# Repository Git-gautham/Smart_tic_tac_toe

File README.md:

# ESP8266 XOX Game (Tic-Tac-Toe)

A two-player Tic-Tac-Toe game built using an ESP8266 NodeMCU board, 5 physical push buttons, and a Wi-Fi-based web interface — no need for external hosting or filesystem upload!

## 🔧 Features

- 🕹️ **Real-time interaction** with physical buttons:
  - `UP`, `LEFT`, `RIGHT`, `SELECT`, and `DOWN` (optional)
- 🌐 **Access via browser** — ESP8266 runs in AP (Access Point) mode
- 🧠 Smart in-browser UI:
  - Grid highlighting with cursor
  - Tracks turns for `X` and `O`
  - Win/draw detection
  - Scoreboard
  - "Next Game" and "Reset Score" buttons
- 🪛 Simple, detachable hardware via header pins
- 🖥️ No LittleFS or SPIFFS required

---

## 📷 Screenshot

---

## 🖥️ Web Interface

Once powered on:
- Connect to Wi-Fi: `XOX_Game` (password: `12345678`)
- Open browser and go to: [http://192.168.4.1](http://192.168.4.1)

---

## 🔌 Hardware Setup

| Function | NodeMCU Pin | GPIO | Status |
|----------|-------------|------|--------|
| Up       | D1          | 5    | ✅ Connected |
| Left     | D2          | 4    | ✅ Connected |
| Right    | D5          | 14   | ✅ Connected |
| Select   | D6          | 12   | ✅ Connected |
| Down     | D7          | 13   | ✅ Connected |

**ESP8266 Dev Board:** NodeMCU v1.0 (ESP-12E module)  
**Buttons:** Tactile push buttons
**Hardware simulation :

!!Down button is not placed due to certain technical difficulties

---

## 🛠️ Schematic (KiCad)

The PCB includes:
- Female headers to plug/unplug NodeMCU
- 5 push buttons connected to GPIOs
- All traces on the bottom side

---

## 🚀 Getting Started

1. Open `src/xox_game.ino` in Arduino IDE
2. Select board: `NodeMCU 1.0 (ESP-12E Module)`
3. Upload the sketch
4. Connect power, join Wi-Fi, and play!

## 🧠 TODO / Improvements

- Add buzzer feedback or LED indicators
- Expand to multiplayer over web (ESP8266 WebSocket)
- Add OLED support

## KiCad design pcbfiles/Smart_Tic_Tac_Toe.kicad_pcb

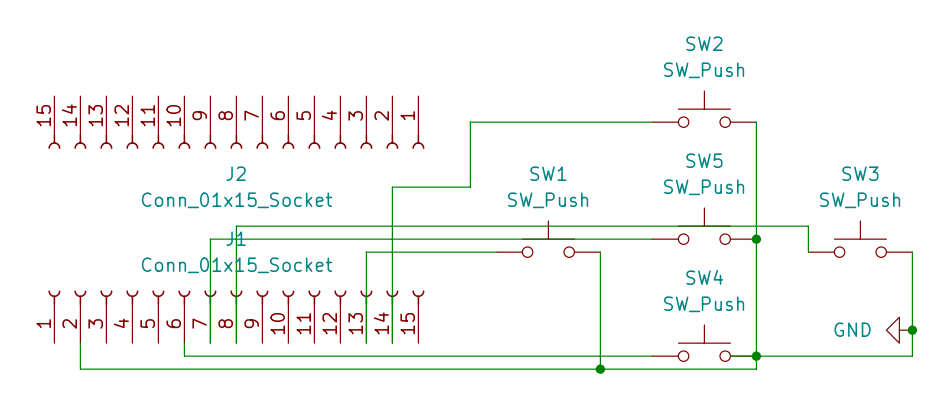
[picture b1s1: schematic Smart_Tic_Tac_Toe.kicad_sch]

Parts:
J1, J2: Conn_01x15_Socket; PinSocket_1x15_P2.54mm_Vertical
SW1, SW2, SW3, SW4, SW5: SW_Push; SW_PUSH_6mm

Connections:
GND: J1.2, SW1.2, SW2.2, SW3.2, SW4.2, SW5.2
unnamed: J1.6, SW4.1
unnamed: J1.7, SW5.1
unnamed: J1.8, SW3.1
unnamed: J1.13, SW1.1
unnamed: J1.14, SW2.1

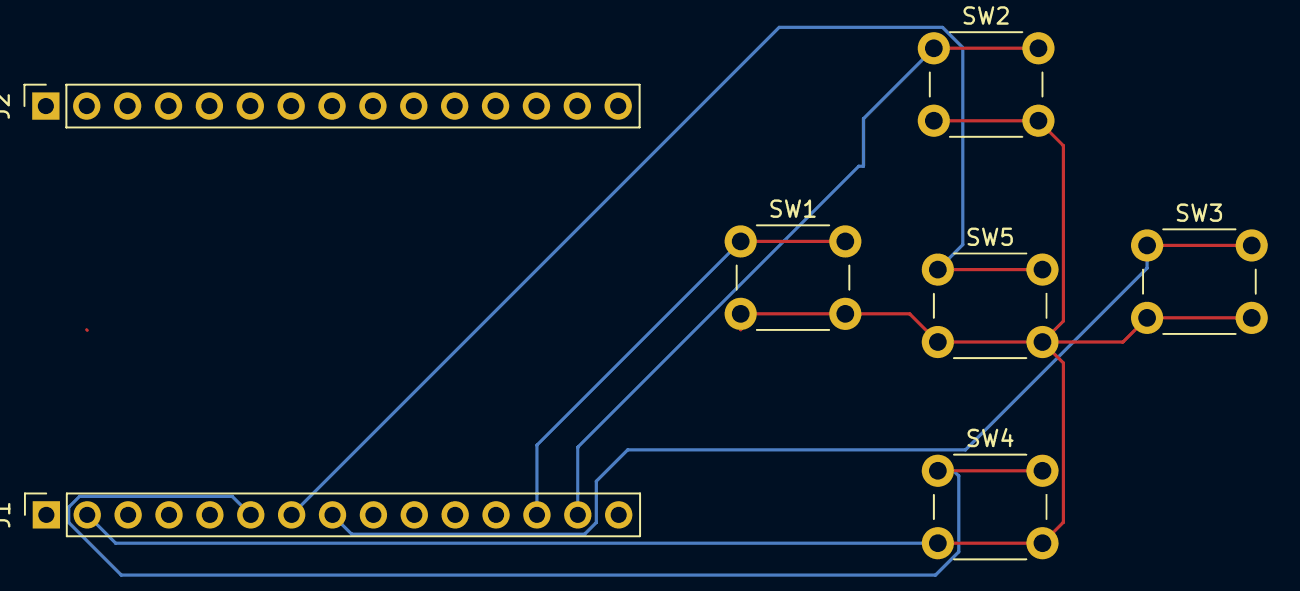
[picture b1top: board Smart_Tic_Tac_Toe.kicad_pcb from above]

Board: 2 copper layers, 7 parts (0 on the bottom side), 6 nets.

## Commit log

2025-06-12 Rename WhatsApp Image 2025-06-12 at 11.34.13_568ad91c.jpg to screenshot1
2025-06-12 Rename WhatsApp Image 2025-06-12 at 11.34.15_2e803093.jpg to circuitdemo
2025-06-12 Rename WhatsApp Image 2025-06-12 at 11.34.14_3d9d58dc.jpg to screenshot2
2025-06-12 Rename WhatsApp Image 2025-06-12 at 11.34.14_16716f99.jpg to screenshot3
2025-06-12 Rename WhatsApp Image 2025-06-12 at 11.34.13_a73f098f.jpg to screenshot4
2025-06-12 Create aa
2025-06-12 Rename xox.ino to src/xox.ino
2025-06-12 Add files via upload
    Has few DRC issues etc to be fixed
